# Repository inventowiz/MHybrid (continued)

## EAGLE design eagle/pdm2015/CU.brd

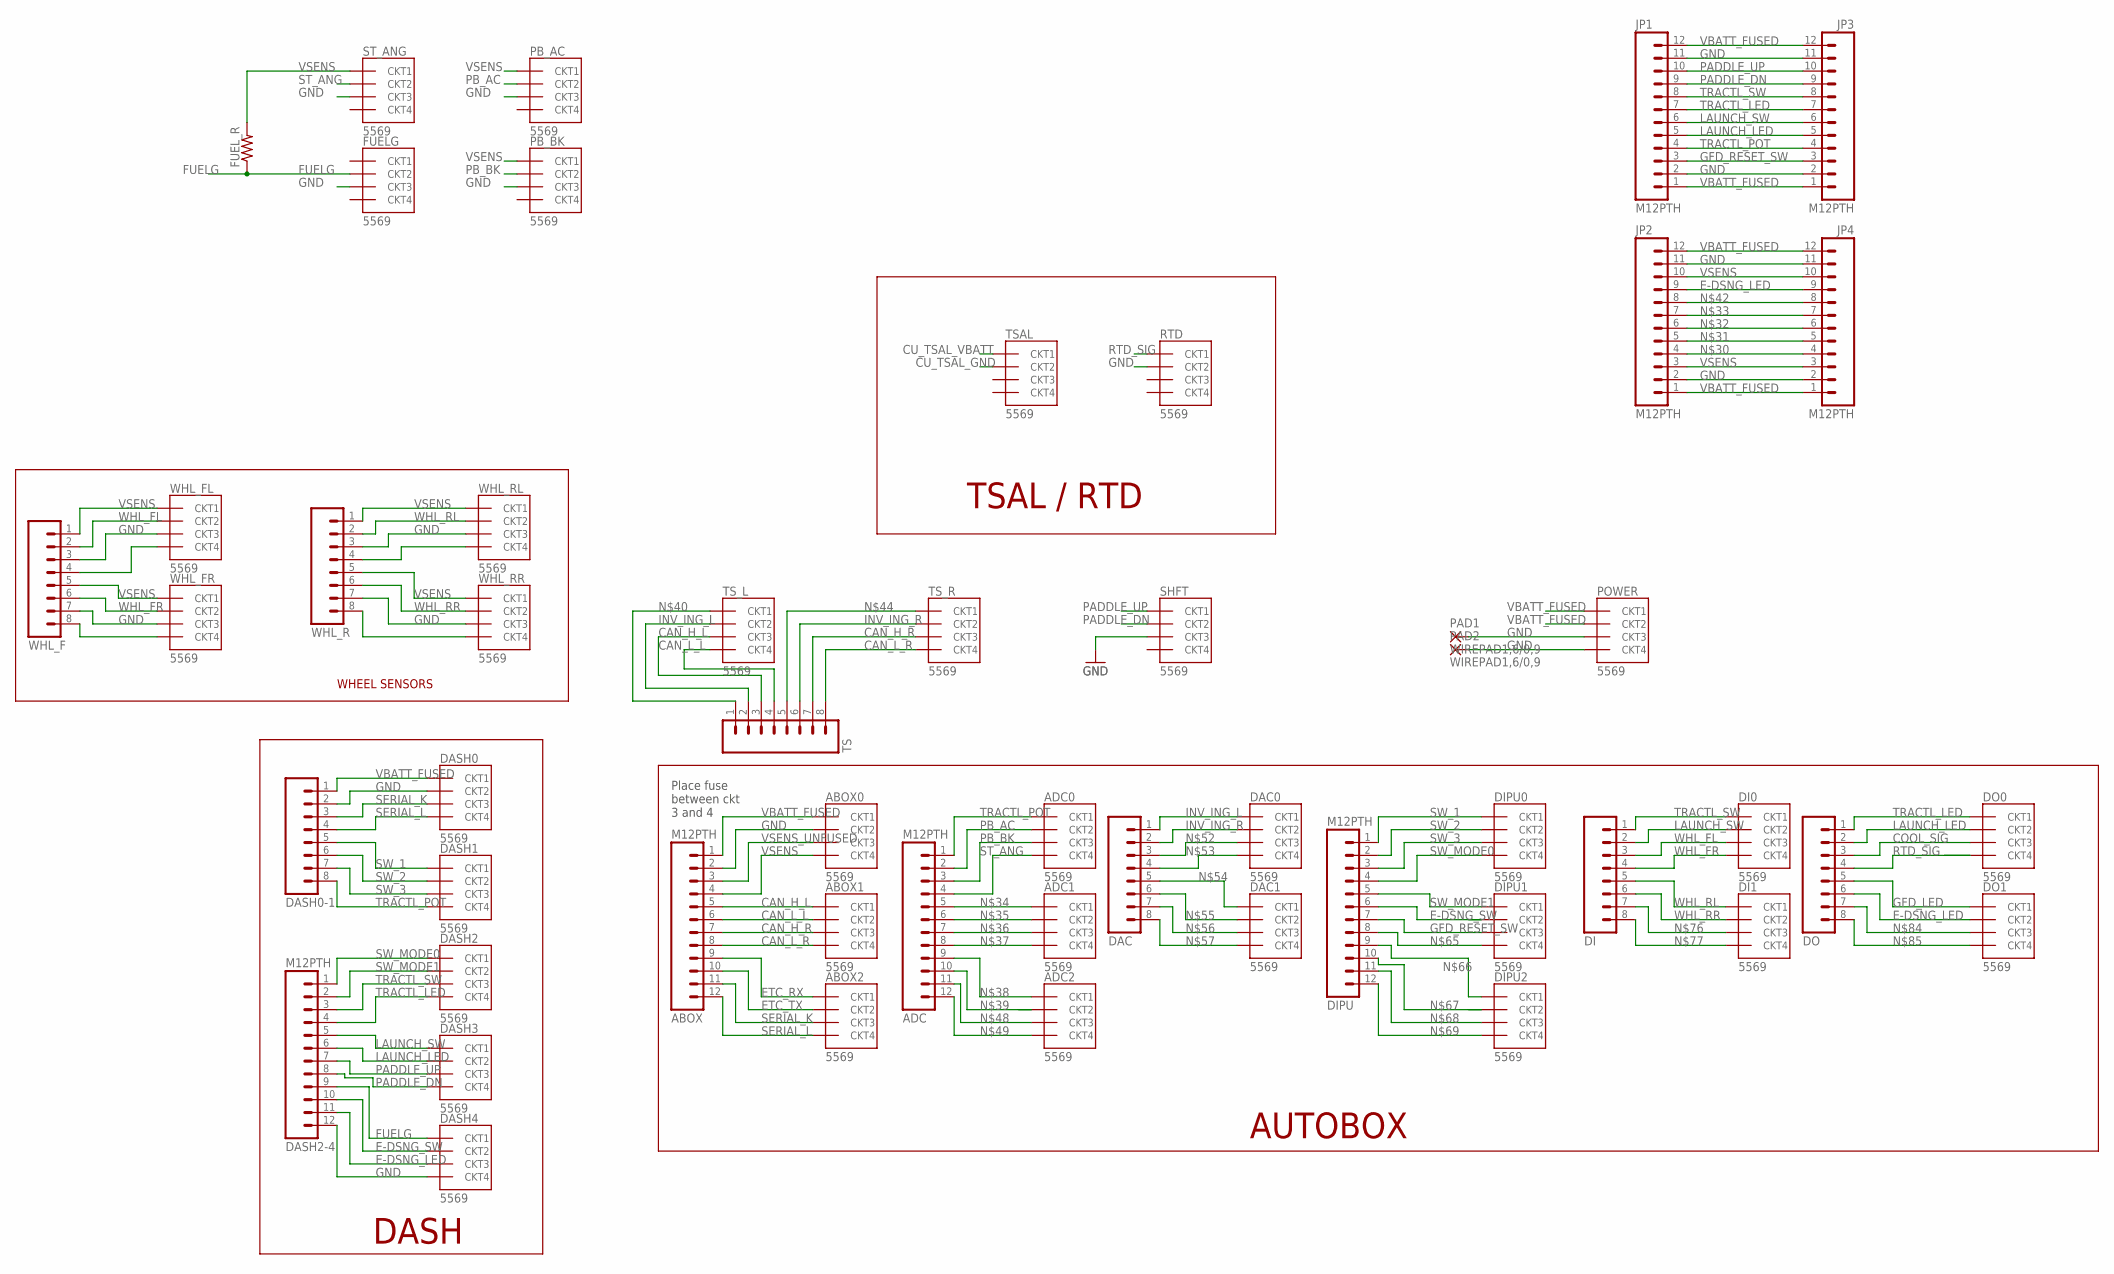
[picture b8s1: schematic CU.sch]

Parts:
ABOX: M12PTH; 1X12
ABOX0, ABOX1, ABOX2: 5569
ADC: M12PTH; 1X12
ADC0, ADC1, ADC2: 5569
DAC: M081X08; 1X08
DAC0, DAC1: 5569
DASH0, DASH1, DASH2, DASH3, DASH4: 5569
DASH0-1: M081X08; 1X08
DASH2-4: M12PTH; 1X12
DI: M081X08; 1X08
DI0, DI1: 5569
DIPU: M12PTH; 1X12
DIPU0, DIPU1, DIPU2: 5569
DO: M081X08; 1X08
DO0, DO1: 5569
FUELG: 5569
FUEL_R: R-US_0204/7; 0204/7
JP1, JP2, JP3, JP4: M12PTH; 1X12
PAD1, PAD2: WIREPAD1,6/0,9; 1,6/0,9
PB_AC: 5569
PB_BK: 5569
POWER: 5569
RTD: 5569
SHFT: 5569
ST_ANG: 5569
TS: M081X08; 1X08
TSAL: 5569
TS_L: 5569
TS_R: 5569
WHL_F: M081X08; 1X08
WHL_FL: 5569
WHL_FR: 5569
WHL_R: M081X08; 1X08
WHL_RL: 5569
WHL_RR: 5569

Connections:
CAN_H_L: ABOX.5, ABOX1.CKT1, TS.3, TS_L.CKT3
CAN_H_R: ABOX.7, ABOX1.CKT3, TS.7, TS_R.CKT3
CAN_L_L: ABOX.6, ABOX1.CKT2, TS.4, TS_L.CKT4
CAN_L_R: ABOX.8, ABOX1.CKT4, TS.8, TS_R.CKT4
COOL_SIG: DO.3, DO0.CKT3
CU_TSAL_GND: TSAL.CKT2
CU_TSAL_VBATT: TSAL.CKT1
E-DSNG_LED: DASH2-4.11, DASH4.CKT3, DO.6, DO1.CKT2, JP2.9, JP4.9
E-DSNG_SW: DASH2-4.10, DASH4.CKT2, DIPU.6, DIPU1.CKT2
ETC_RX: ABOX.9, ABOX2.CKT1
ETC_TX: ABOX.10, ABOX2.CKT2
FUELG: DASH2-4.9, DASH4.CKT1, FUELG.CKT2, FUEL_R.1
GFD_LED: DO.5, DO1.CKT1
GFD_RESET_SW: DIPU.7, DIPU1.CKT3, JP1.3, JP3.3
GND: ABOX.2, ABOX0.CKT2, DASH0.CKT2, DASH0-1.2, DASH2-4.12, DASH4.CKT4, FUELG.CKT3, JP1.2, JP1.11, JP2.2, JP2.11, JP3.2, JP3.11, JP4.2, JP4.11, PAD1.1, PAD2.1, PB_AC.CKT3, PB_BK.CKT3, POWER.CKT3, POWER.CKT4, RTD.CKT2, SHFT.CKT3, ST_ANG.CKT3, WHL_F.3, WHL_F.7, WHL_FL.CKT3, WHL_FR.CKT3, WHL_R.3, WHL_R.7, WHL_RL.CKT3, WHL_RR.CKT3
INV_ING_L: DAC.1, DAC0.CKT1, TS.2, TS_L.CKT2
INV_ING_R: DAC.2, DAC0.CKT2, TS.6, TS_R.CKT2
LAUNCH_LED: DASH2-4.6, DASH3.CKT2, DO.2, DO0.CKT2, JP1.5, JP3.5
LAUNCH_SW: DASH2-4.5, DASH3.CKT1, DI.2, DI0.CKT2, JP1.6, JP3.6
unnamed: WHL_F.4, WHL_FL.CKT4
unnamed: WHL_F.8, WHL_FR.CKT4
unnamed: WHL_R.8, WHL_RR.CKT4
unnamed: WHL_R.4, WHL_RL.CKT4
unnamed: JP2.4, JP4.4
unnamed: JP2.5, JP4.5
unnamed: JP2.6, JP4.6
unnamed: JP2.7, JP4.7
unnamed: ADC.5, ADC1.CKT1
unnamed: ADC.6, ADC1.CKT2
unnamed: ADC.7, ADC1.CKT3
unnamed: ADC.8, ADC1.CKT4
unnamed: ADC.9, ADC2.CKT1
unnamed: ADC.10, ADC2.CKT2
unnamed: TS.1, TS_L.CKT1
unnamed: JP2.8, JP4.8
unnamed: TS.5, TS_R.CKT1
unnamed: ADC.11, ADC2.CKT3
unnamed: ADC.12, ADC2.CKT4
unnamed: DAC.3, DAC0.CKT3
unnamed: DAC.4, DAC0.CKT4
unnamed: DAC.5, DAC1.CKT1
unnamed: DAC.6, DAC1.CKT2
unnamed: DAC.7, DAC1.CKT3
unnamed: DAC.8, DAC1.CKT4
unnamed: DIPU.8, DIPU1.CKT4
unnamed: DIPU.9, DIPU2.CKT1
unnamed: DIPU.10, DIPU2.CKT2
unnamed: DIPU.11, DIPU2.CKT3
unnamed: DIPU.12, DIPU2.CKT4
unnamed: DI.7, DI1.CKT3
unnamed: DI.8, DI1.CKT4
unnamed: DO.7, DO1.CKT3
unnamed: DO.8, DO1.CKT4
PADDLE_DN: DASH2-4.8, DASH3.CKT4, JP1.9, JP3.9, SHFT.CKT2
PADDLE_UP: DASH2-4.7, DASH3.CKT3, JP1.10, JP3.10, SHFT.CKT1
PB_AC: ADC.2, ADC0.CKT2, PB_AC.CKT2
PB_BK: ADC.3, ADC0.CKT3, PB_BK.CKT2
RTD_SIG: DO.4, DO0.CKT4, RTD.CKT1
SERIAL_K: ABOX.11, ABOX2.CKT3, DASH0.CKT3, DASH0-1.3
SERIAL_L: ABOX.12, ABOX2.CKT4, DASH0.CKT4, DASH0-1.4
ST_ANG: ADC.4, ADC0.CKT4, ST_ANG.CKT2
SW_1: DASH0-1.5, DASH1.CKT1, DIPU.1, DIPU0.CKT1
SW_2: DASH0-1.6, DASH1.CKT2, DIPU.2, DIPU0.CKT2
SW_3: DASH0-1.7, DASH1.CKT3, DIPU.3, DIPU0.CKT3
SW_MODE0: DASH2.CKT1, DASH2-4.1, DIPU.4, DIPU0.CKT4
SW_MODE1: DASH2.CKT2, DASH2-4.2, DIPU.5, DIPU1.CKT1
TRACTL_LED: DASH2.CKT4, DASH2-4.4, DO.1, DO0.CKT1, JP1.7, JP3.7
TRACTL_POT: ADC.1, ADC0.CKT1, DASH0-1.8, DASH1.CKT4, JP1.4, JP3.4
TRACTL_SW: DASH2.CKT3, DASH2-4.3, DI.1, DI0.CKT1, JP1.8, JP3.8
VBATT_FUSED: ABOX.1, ABOX0.CKT1, DASH0.CKT1, DASH0-1.1, JP1.1, JP1.12, JP2.1, JP2.12, JP3.1, JP3.12, JP4.1, JP4.12, POWER.CKT1, POWER.CKT2
VSENS: ABOX.4, ABOX0.CKT4, FUEL_R.2, JP2.3, JP2.10, JP4.3, JP4.10, PB_AC.CKT1, PB_BK.CKT1, ST_ANG.CKT1, WHL_F.1, WHL_F.5, WHL_FL.CKT1, WHL_FR.CKT1, WHL_R.1, WHL_R.5, WHL_RL.CKT1, WHL_RR.CKT1
VSENS_UNFUSED: ABOX.3, ABOX0.CKT3
WHL_FL: DI.3, DI0.CKT3, WHL_F.2, WHL_FL.CKT2
WHL_FR: DI.4, DI0.CKT4, WHL_F.6, WHL_FR.CKT2
WHL_RL: DI.5, DI1.CKT1, WHL_R.2, WHL_RL.CKT2
WHL_RR: DI.6, DI1.CKT2, WHL_R.6, WHL_RR.CKT2

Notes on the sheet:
WHEEL SENSORS
TSAL / RTD
AUTOBOX
DASH
Place fuse between ckt 3 and 4

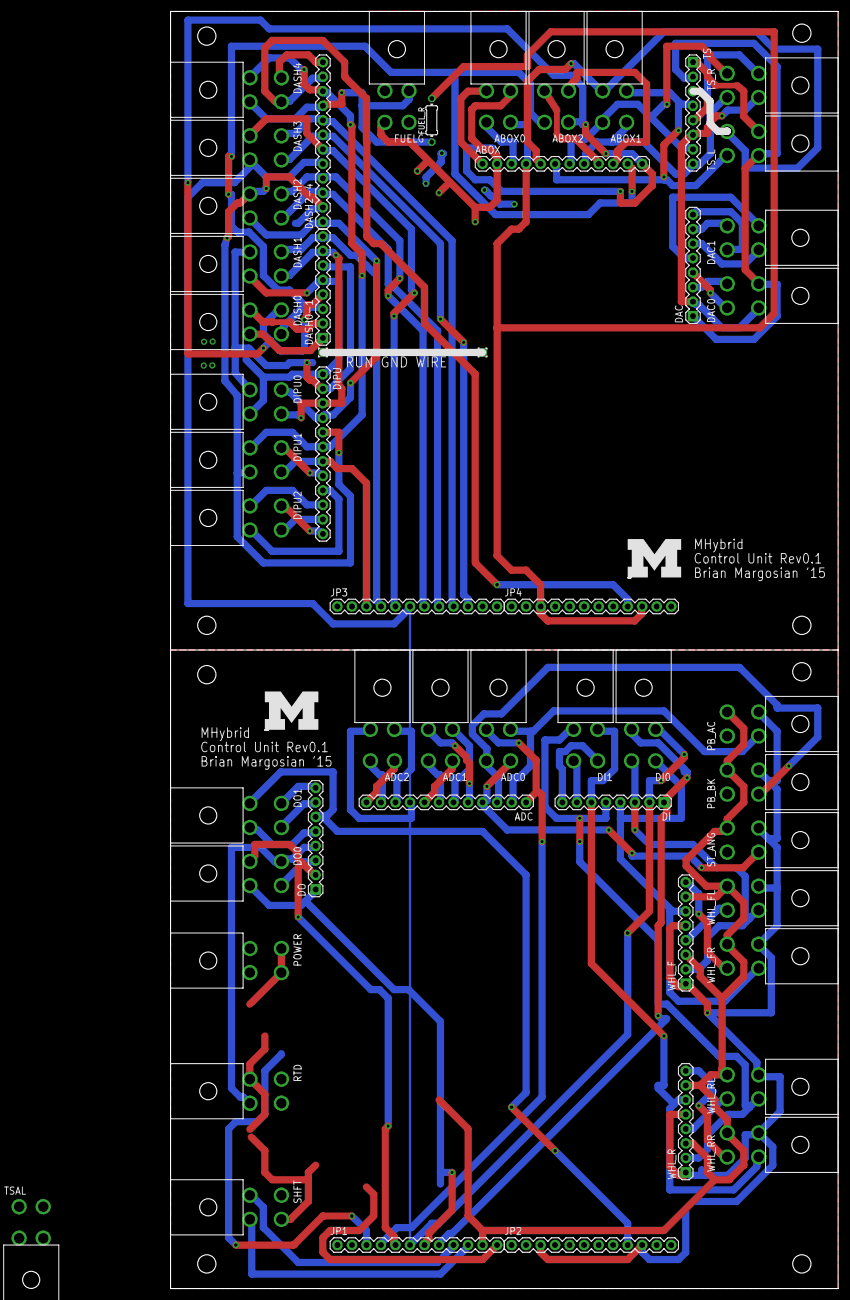
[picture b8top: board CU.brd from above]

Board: 3 copper layers, 116.8 x 223.5 mm, 54 parts (0 on the bottom side), 74 nets.

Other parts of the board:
U$2, U$3: BLOCKM

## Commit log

2014-01-19 Moved .gitignore into the eagle dir
2014-01-23 added Mega Shield
2014-01-23 Added eagle mega shield
2014-01-23 working on pcb, added main connector and lcds
2014-01-25 more changes
2014-02-05 did a lot of pcb work
2014-02-15 lots of board work
2014-03-11 ordered pcbs
2014-04-19 added dash code and updated docs
2014-04-19 fixed file structure
2014-04-22 updated dash code
2014-04-22 updated code
2014-04-26 added files
2014-04-26 working on dash code, k-line now works
2014-04-27 worked more on dash. fuelg needs more work, but serial communication is 100%
2014-04-27 minor fix
2014-10-29 2015 CU eagle files
2014-10-29 updated old CU and pdfs
2014-11-26 updated files and added MHR15 documents
2014-12-10 added initial v0 of Inverter Current Sensor PCB
2014-12-29 updated libraries for GLV power & TS
2014-12-31 created current sensor PCB v1
2015-01-14 updated current sensor board and GLV_PWR simulation
2015-01-20 updated board, but this version violates clearance
2015-01-21 finalized v1 of current sensor board
2015-01-21 Rearranged files in prep for 2015
2015-01-21 modified readme
2015-02-06 Finalized v2 of inverter current sensor board
2015-02-18 Brian' s updates 2-17-15
2015-02-18 Lots of work on simulink diagrams for communication
2015-02-24 added HV PCB and inverter DC current sensor PCB
2015-03-26 March update
2015-03-27 added some EAGLE
2015-04-06 Added Dash communication block, worked on rear CAN module, added beginnings of race crew shirts
2015-04-16 added inverter communication subsystems, modified radio system
2015-04-16 modified logos and rear can module code
2015-04-18 Updated BMS and Inverter blockset
2015-04-18 updated inverter blockset
2015-04-23 modified dash and inverter simulink blocks
